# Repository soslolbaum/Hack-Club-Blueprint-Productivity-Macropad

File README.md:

# Hack-Club-Blueprint-Productivity-Macropad
A Macropad designed for improving productivity and workflow on Linux.
Can and will be used for working on projects, hobbies homework ect...
Multiple buttons connected to rotary encoders to switch their functionality.
Features like:
       Execute a script that blocks distracting apps for 30 minutes
       Toggle do not disturb mode
       Toggle WiFi/VPN/Firewall
       Control brightness
       Switch arround workspaces
       Open project applications like GitHub, Blender, ArduinoIDE...
       Backup predetermined folders using Git/GitHub
and hopefully even more features to come!

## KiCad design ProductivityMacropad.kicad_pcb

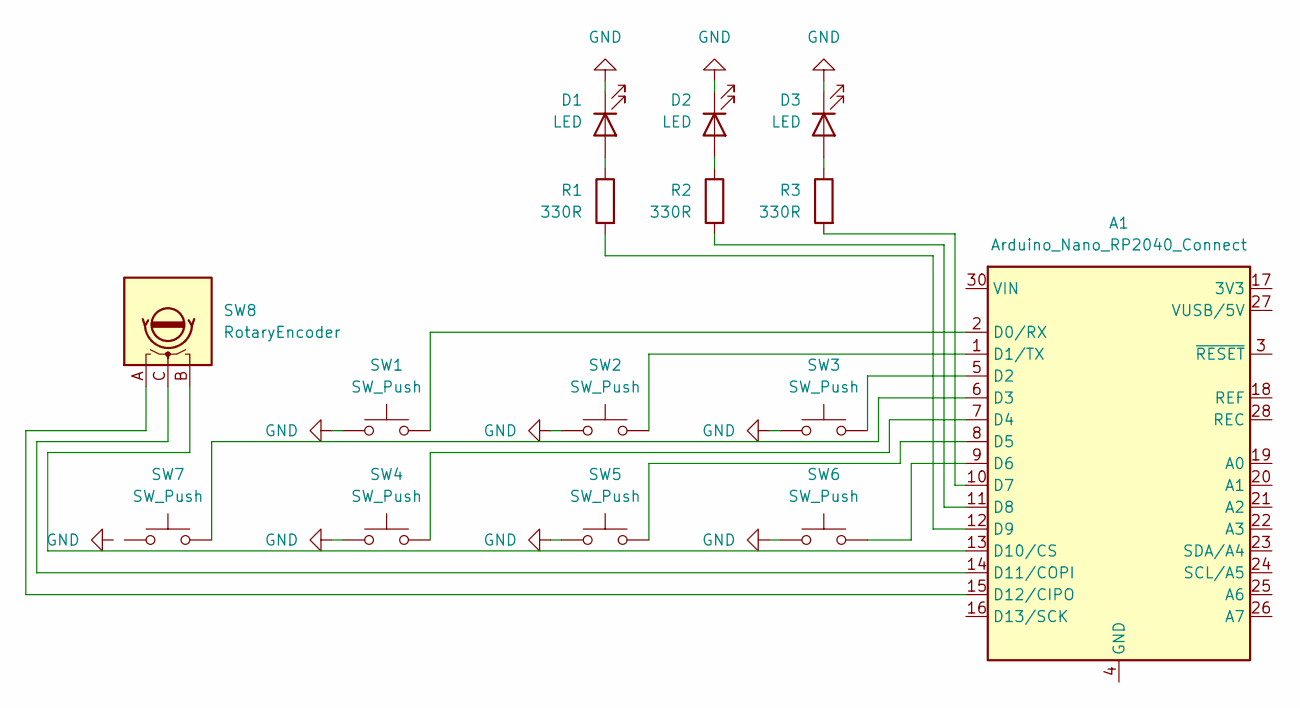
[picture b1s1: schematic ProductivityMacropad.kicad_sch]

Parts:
A1: Arduino_Nano_RP2040_Connect; Arduino_Nano
D1, D2, D3: LED; LED_D3.0mm
R1, R2, R3: 330R; R_Axial_DIN0207_L6.3mm_D2.5mm_P10.16mm_Horizontal
SW1, SW2, SW3, SW4, SW5, SW6, SW7: SW_Push; SW_Cherry_MX_1.00u_PCB
SW8: RotaryEncoder; RotaryEncoder_Bourns_Horizontal_PEC09-2xxxF-Nxxxx

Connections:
GND: D1.1 (K), D2.1 (K), D3.1 (K), SW1.1, SW2.1, SW3.1, SW4.1, SW5.1, SW6.1
unnamed: A1.2 (D0/RX), SW1.2
unnamed: A1.1 (D1/TX), SW2.2
unnamed: A1.5 (D2), SW3.2
unnamed: A1.6 (D3), SW7.2
unnamed: A1.7 (D4), SW4.2
unnamed: A1.8 (D5), SW5.2
unnamed: A1.9 (D6), SW6.2
unnamed: A1.10 (D7), R3.2
unnamed: A1.11 (D8), R2.2
unnamed: A1.12 (D9), R1.2
unnamed: A1.13 (D10/CS), SW8.B
unnamed: A1.14 (D11/COPI), SW8.C
unnamed: A1.15 (D12/CIPO), SW8.A
unnamed: A1.4 (GND), A1.29 (GND)
unnamed: D1.2 (A), R1.1
unnamed: D2.2 (A), R2.1
unnamed: D3.2 (A), R3.1

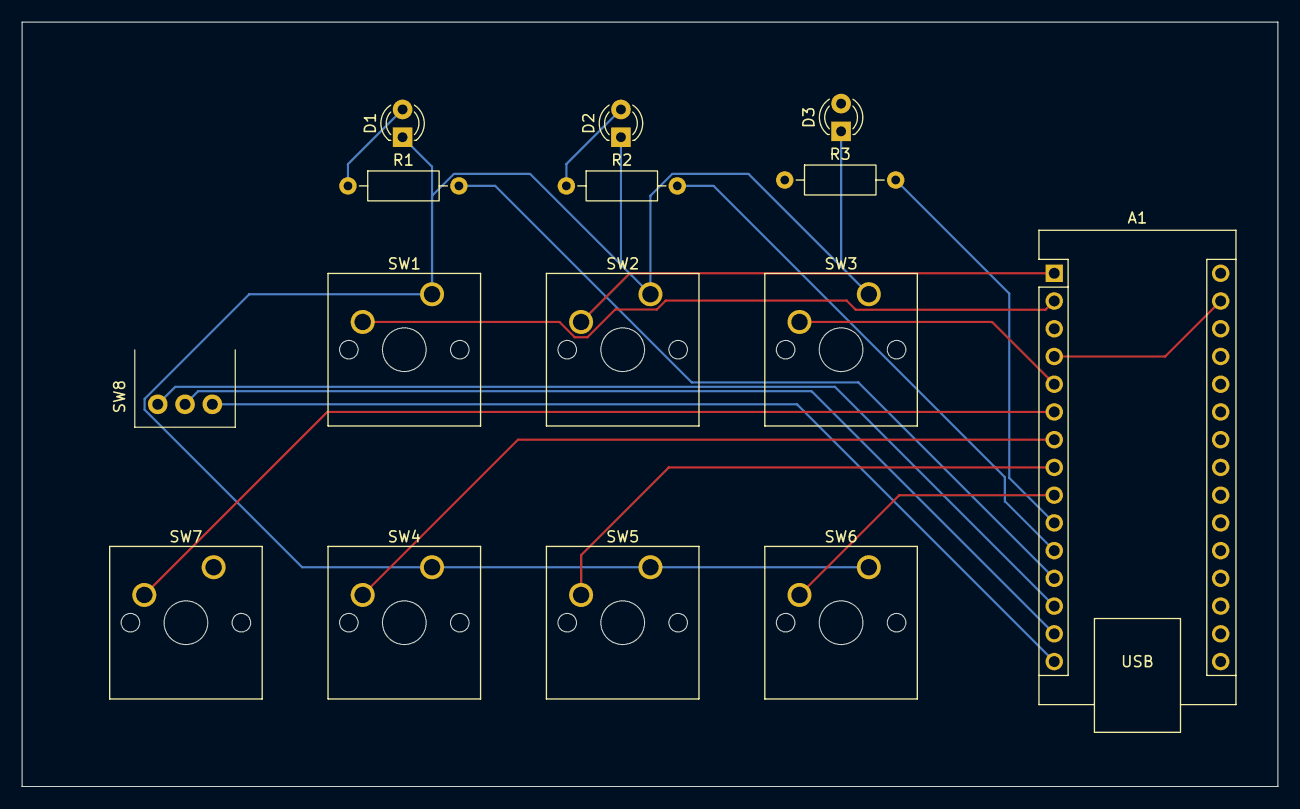
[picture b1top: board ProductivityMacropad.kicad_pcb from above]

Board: 2 copper layers, 115.0 x 70.0 mm, 15 parts (0 on the bottom side), 18 nets.

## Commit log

2026-02-22 Enhance README with project details and features
    Added a project description and features list for the Macropad.
2026-02-22 Added 2 Files
    Added Schematic and PCB file
2026-02-22 Updated PCB
2026-02-22 Updated faulty PCB (again)
